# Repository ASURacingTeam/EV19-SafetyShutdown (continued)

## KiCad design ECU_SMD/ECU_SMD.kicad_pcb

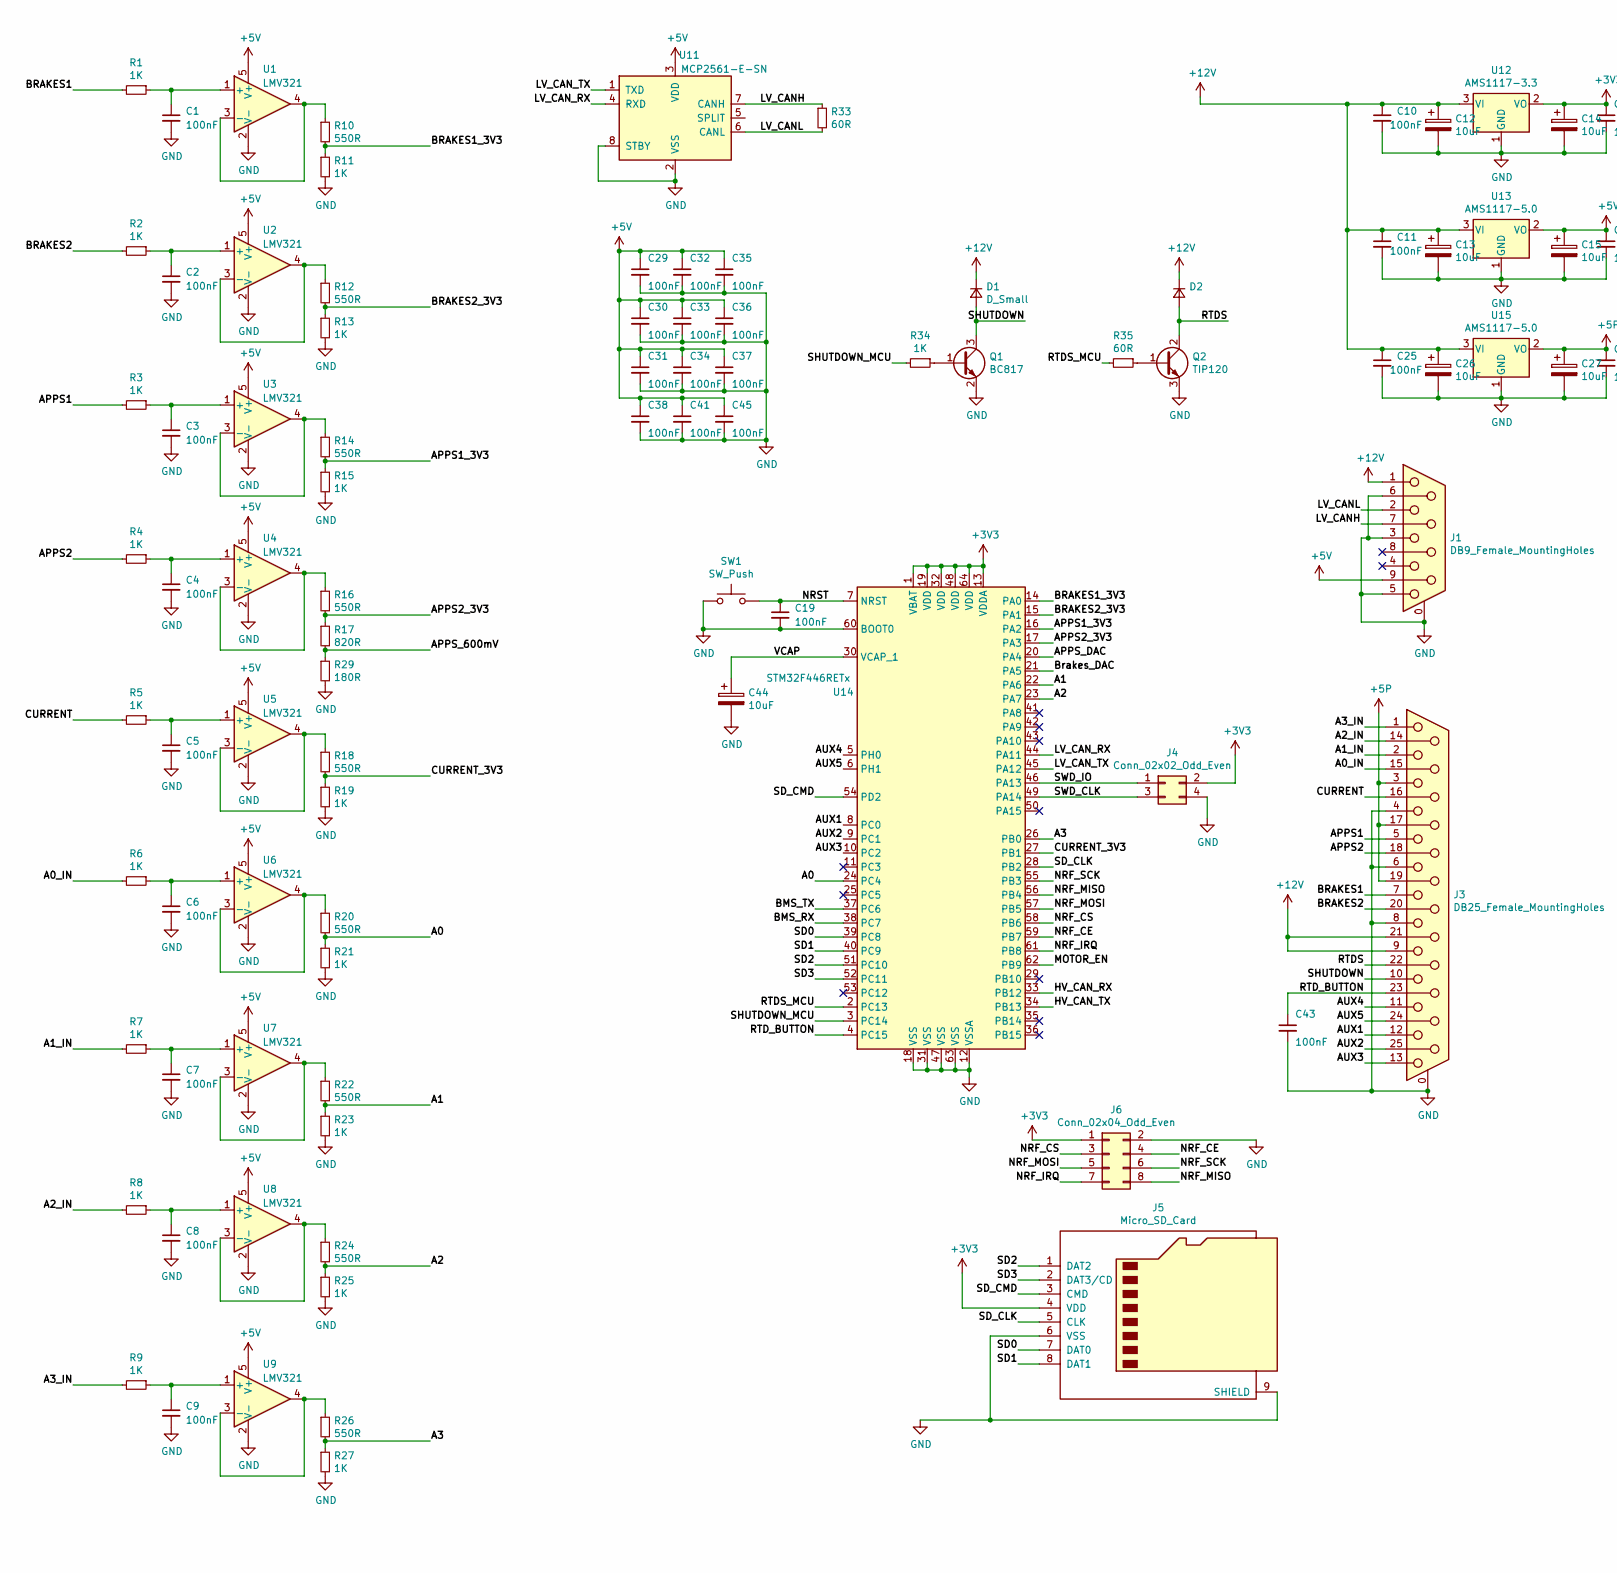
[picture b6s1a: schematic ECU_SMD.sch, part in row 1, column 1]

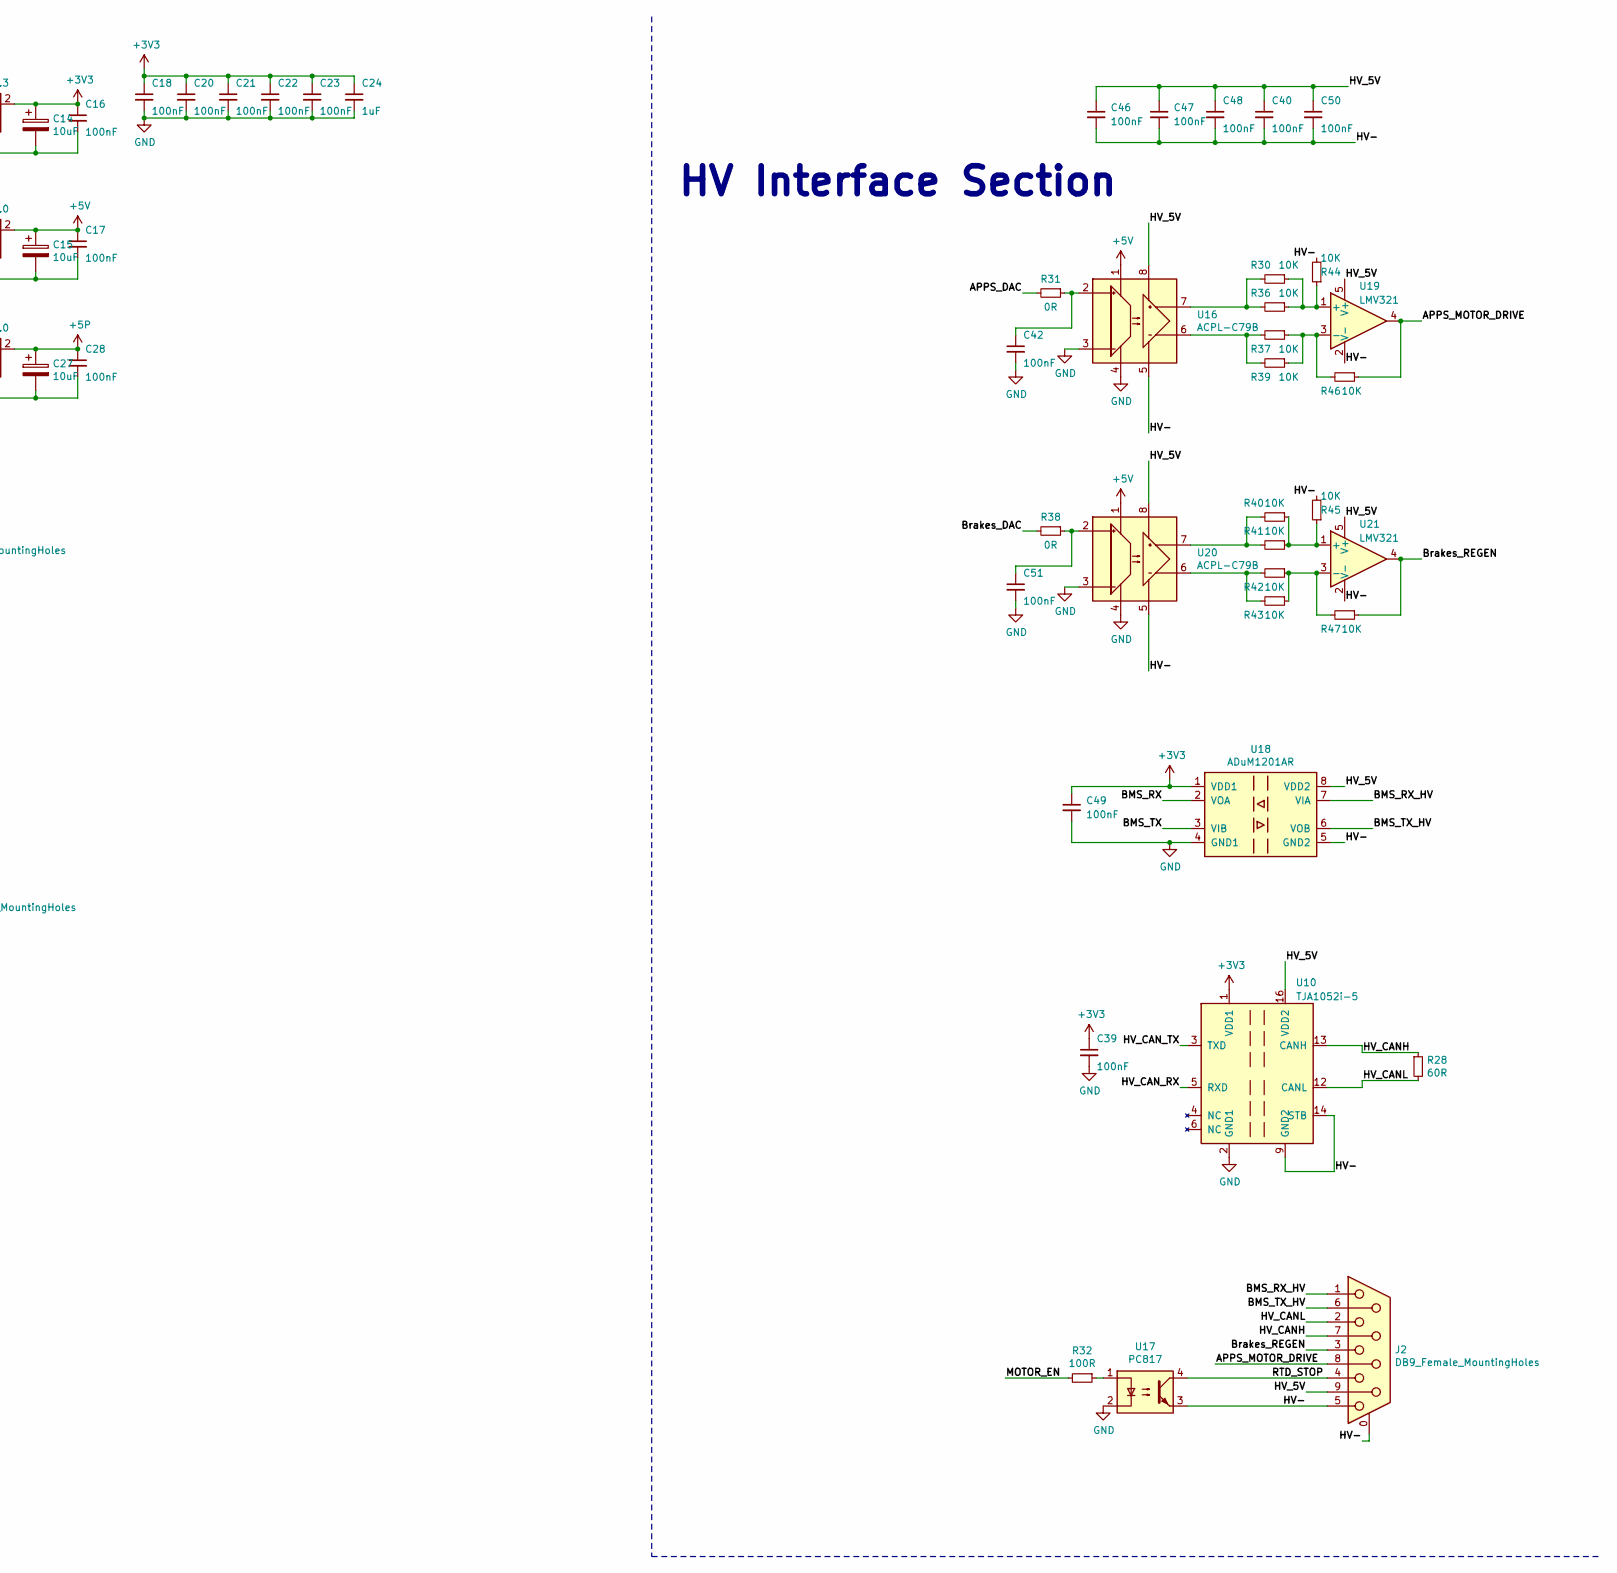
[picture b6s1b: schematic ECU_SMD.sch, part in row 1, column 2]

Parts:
C1, C2, C3, C4, C5, C6, C7, C8, C9, C10, C11, C16, C17, C18, C19, C20, C21, C22, C23, C25, C28, C29, C30, C31, C32, C33, C34, C35, C36, C37, C38, C39, C40, C41, C42, C43, C45, C46, C47, C48, C49, C50, C51: 100nF; C_0805_2012Metric_Pad1.15x1.40mm_HandSolder
C12, C13, C14, C15, C26, C27, C44: 10uF; C_1206_3216Metric_Pad1.42x1.75mm_HandSolder
C24: 1uF; C_0805_2012Metric_Pad1.15x1.40mm_HandSolder
D1: D_Small; D_A-405_P10.16mm_Horizontal
D2: a; D_A-405_P10.16mm_Horizontal
J1, J2: DB9_Female_MountingHoles; DSUB-9_Female_Horizontal_P2.77x2.84mm_EdgePinOffset4.94mm_H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
J3: DB25_Female_MountingHoles; DSUB-25_Female_Horizontal_P2.77x2.84mm_EdgePinOffset4.94mm_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
J4: Conn_02x02_Odd_Even; PinHeader_2x02_P2.54mm_Vertical
J5: Micro_SD_Card; microSD_HC_Hirose_DM3AT-SF-PEJM5
J6: Conn_02x04_Odd_Even; PinHeader_2x04_P2.54mm_Vertical
Q1: BC817; SOT-23
Q2: TIP120; TO-220-3_Horizontal_TabDown
R1, R2, R3, R4, R5, R6, R7, R8, R9, R11, R13, R15, R19, R21, R23, R25, R27, R34: 1K; R_0805_2012Metric_Pad1.15x1.40mm_HandSolder
R10, R12, R14, R16, R18, R20, R22, R24, R26: 550R; R_0805_2012Metric_Pad1.15x1.40mm_HandSolder
R17: 820R; R_0805_2012Metric_Pad1.15x1.40mm_HandSolder
R28, R33, R35: 60R; R_0805_2012Metric_Pad1.15x1.40mm_HandSolder
R29: 180R; R_0805_2012Metric_Pad1.15x1.40mm_HandSolder
R30, R36, R37, R39, R40, R41, R42, R43, R44, R45, R46, R47: 10K; R_0805_2012Metric_Pad1.15x1.40mm_HandSolder
R31, R38: 0R; R_0805_2012Metric_Pad1.15x1.40mm_HandSolder
R32: 100R; R_0805_2012Metric_Pad1.15x1.40mm_HandSolder
SW1: SW_Push; R_0805_2012Metric_Pad1.15x1.40mm_HandSolder
U1, U2, U3, U4, U5, U6, U7, U8, U9, U19, U21: LMV321; SOT-23-5_HandSoldering
U10: TJA1052i-5; SOIC-16W_7.5x10.3mm_P1.27mm
U11: MCP2561-E-SN; SOIC-8_3.9x4.9mm_P1.27mm
U12: AMS1117-3.3; SOT-223-3_TabPin2
U13, U15: AMS1117-5.0; SOT-223-3_TabPin2
U14: STM32F446RETx; LQFP-64_10x10mm_P0.5mm
U16, U20: ACPL-C79B; SSO-8_6.8x5.9mm_P1.27mm_Clearance8mm
U17: PC817; DIP-4_W7.62mm
U18: ADuM1201AR; SOIC-8_3.9x4.9mm_P1.27mm

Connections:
+3V3: C14.1, C16.1, C18.1, C20.1, C21.1, C22.1, C23.1, C24.1, C39.1, C49.1, J4.2, J5.4 (VDD), J6.1, U10.1 (VDD1), U12.2 (VO), U14.1 (VBAT), U14.13 (VDDA), U14.19 (VDD), U14.32 (VDD), U14.48 (VDD), U14.64 (VDD), U18.1 (VDD1)
+5P: C27.1, C28.1, J3.3, J3.17, J3.19, U15.2 (VO)
+5V: C15.1, C17.1, C29.1, C30.1, C31.1, C32.1, C33.1, C34.1, C35.1, C36.1, C37.1, C38.1, C41.1, C45.1, J1.9, U1.5 (V+), U2.5 (V+), U3.5 (V+), U4.5 (V+), U5.5 (V+), U6.5 (V+), U7.5 (V+), U8.5 (V+), U9.5 (V+), U11.3 (VDD), U13.2 (VO), U16.1 (VDD1), U20.1 (VDD1)
+12V: C10.1, C11.1, C12.1, C13.1, C25.1, C26.1, D1.1 (K), D2.1 (K), J1.1, J3.9, J3.21, U12.3 (VI), U13.3 (VI), U15.3 (VI)
/A0: R20.2, R21.1, U14.24 (PC4)
/A0_IN: J3.15, R6.2
/A1: R22.2, R23.1, U14.22 (PA6)
/A1_IN: J3.2, R7.2
/A2: R24.2, R25.1, U14.23 (PA7)
/A2_IN: J3.14, R8.2
/A3: R26.2, R27.1, U14.26 (PB0)
/A3_IN: J3.1, R9.2
/APPS1: J3.5, R3.2
/APPS1_3V3: R14.2, R15.1, U14.16 (PA2)
/APPS2: J3.18, R4.2
/APPS2_3V3: R16.2, R17.1, U14.17 (PA3)
/APPS_600mV: R17.2, R29.1
/APPS_DAC: R31.2, U14.20 (PA4)
/APPS_MOTOR_DRIVE: J2.8, R46.1, U19.4
/AUX1: J3.12, U14.8 (PC0)
/AUX2: J3.25, U14.9 (PC1)
/AUX3: J3.13, U14.10 (PC2)
/AUX4: J3.11, U14.5 (PH0)
/AUX5: J3.24, U14.6 (PH1)
/BMS_RX: U14.38 (PC7), U18.2 (VOA)
/BMS_RX_HV: J2.1, U18.7 (VIA)
/BMS_TX: U14.37 (PC6), U18.3 (VIB)
/BMS_TX_HV: J2.6, U18.6 (VOB)
/BRAKES1: J3.7, R1.2
/BRAKES1_3V3: R10.2, R11.1, U14.14 (PA0)
/BRAKES2: J3.20, R2.2
/BRAKES2_3V3: R12.2, R13.1, U14.15 (PA1)
/Brakes_DAC: R38.2, U14.21 (PA5)
/Brakes_REGEN: J2.3, R47.1, U21.4
/CURRENT: J3.16, R5.2
/CURRENT_3V3: R18.2, R19.1, U14.27 (PB1)
/HV-: C40.2, C46.2, C47.2, C48.2, C50.2, J2.0 (PAD), J2.5, R44.2, R45.2, U10.9 (GND2), U10.10 (GND2), U10.14 (STB), U10.15 (GND2), U16.5 (GND2), U17.3, U18.5 (GND2), U19.2 (V-), U20.5 (GND2), U21.2 (V-)
/HV_5V: C40.1, C46.1, C47.1, C48.1, C50.1, J2.9, U10.11 (VDD2), U10.16 (VDD2), U16.8 (VDD2), U18.8 (VDD2), U19.5 (V+), U20.8 (VDD2), U21.5 (V+)
/HV_CANH: J2.7, R28.1, U10.13 (CANH)
/HV_CANL: J2.2, R28.2, U10.12 (CANL)
/HV_CAN_RX: U10.5 (RXD), U14.33 (PB12)
/HV_CAN_TX: U10.3 (TXD), U14.34 (PB13)
/LV_CANH: J1.7, R33.1, U11.7 (CANH)
/LV_CANL: J1.2, R33.2, U11.6 (CANL)
/LV_CAN_RX: U11.4 (RXD), U14.44 (PA11)
/LV_CAN_TX: U11.1 (TXD), U14.45 (PA12)
/MOTOR_EN: R32.2, U14.62 (PB9)
/NRF_CE: J6.4, U14.59 (PB7)
/NRF_CS: J6.3, U14.58 (PB6)
/NRF_IRQ: J6.7, U14.61 (PB8)
/NRF_MISO: J6.8, U14.56 (PB4)
/NRF_MOSI: J6.5, U14.57 (PB5)
/NRF_SCK: J6.6, U14.55 (PB3)
/NRST: C19.1, SW1.2, U14.7 (NRST)
/RTDS: D2.2 (A), J3.22, Q2.2 (C)
/RTDS_MCU: R35.2, U14.2 (PC13)
/RTD_BUTTON: C43.1, J3.23, U14.4 (PC15)
/RTD_STOP: J2.4, U17.4
/SD0: J5.7 (DAT0), U14.39 (PC8)
/SD1: J5.8 (DAT1), U14.40 (PC9)
/SD2: J5.1 (DAT2), U14.51 (PC10)
/SD3: J5.2 (DAT3/CD), U14.52 (PC11)
/SD_CLK: J5.5 (CLK), U14.28 (PB2)
/SD_CMD: J5.3 (CMD), U14.54 (PD2)
/SHUTDOWN: D1.2 (A), J3.10, Q1.3 (C)
/SHUTDOWN_MCU: R34.2, U14.3 (PC14)
/SWD_CLK: J4.3, U14.49 (PA14)
/SWD_IO: J4.1, U14.46 (PA13)
/VCAP: C44.1, U14.30 (VCAP_1)
GND: C1.2, C2.2, C3.2, C4.2, C5.2, C6.2, C7.2, C8.2, C9.2, C10.2, C11.2, C12.2, C13.2, C14.2, C15.2, C16.2, C17.2, C18.2, C19.2, C20.2, C21.2, C22.2, C23.2, C24.2, C25.2, C26.2, C27.2, C28.2, C29.2, C30.2, C31.2, C32.2, C33.2, C34.2, C35.2, C36.2, C37.2, C38.2, C39.2, C41.2, C42.2, C43.2, C44.2, C45.2, C49.2, C51.2, J1.0 (PAD), J1.3, J1.5, J1.6, J3.0 (PAD), J3.4, J3.6, J3.8, J4.4, J5.6 (VSS), J5.9 (SHIELD), J6.2, Q1.2 (E), Q2.3 (E), R11.2, R13.2, R15.2, R19.2, R21.2, R23.2, R25.2, R27.2, R29.2, SW1.1, U1.2 (V-), U2.2 (V-), U3.2 (V-), U4.2 (V-), U5.2 (V-), U6.2 (V-), U7.2 (V-), U8.2 (V-), U9.2 (V-), U10.2 (GND1), U10.7 (GND1), U10.8 (GND1), U11.2 (VSS), U11.8 (STBY), U12.1 (GND), U13.1 (GND), U14.12 (VSSA), U14.18 (VSS), U14.31 (VSS), U14.47 (VSS), U14.60 (BOOT0), U14.63 (VSS), U15.1 (GND), U16.3 (IN-), U16.4 (GND1), U17.2, U18.4 (GND1), U20.3 (IN-), U20.4 (GND1)
unnamed: C1.1, R1.1, U1.1 (+)
unnamed: C2.1, R2.1, U2.1 (+)
unnamed: C3.1, R3.1, U3.1 (+)
unnamed: C4.1, R4.1, U4.1 (+)
unnamed: C5.1, R5.1, U5.1 (+)
unnamed: C6.1, R6.1, U6.1 (+)
unnamed: C7.1, R7.1, U7.1 (+)
unnamed: C8.1, R8.1, U8.1 (+)
unnamed: C9.1, R9.1, U9.1 (+)
unnamed: C42.1, R31.1, U16.2 (IN+)
unnamed: C51.1, R38.1, U20.2 (IN+)
unnamed: Q1.1 (B), R34.1
unnamed: Q2.1 (B), R35.1
unnamed: R10.1, U1.3 (-), U1.4
unnamed: R12.1, U2.3 (-), U2.4
unnamed: R14.1, U3.3 (-), U3.4
unnamed: R16.1, U4.3 (-), U4.4
unnamed: R18.1, U5.3 (-), U5.4
unnamed: R20.1, U6.3 (-), U6.4
unnamed: R22.1, U7.3 (-), U7.4
unnamed: R24.1, U8.3 (-), U8.4
unnamed: R26.1, U9.3 (-), U9.4
unnamed 92: R30.1, R36.1, R44.1, U19.1 (+); also elsewhere on the board
unnamed 93: R30.2, R36.2, U16.7 (OUT+); also elsewhere on the board
unnamed: R32.1, U17.1
unnamed: R37.1, R39.1, R46.2, U19.3 (-)
unnamed: R37.2, R39.2, U16.6 (OUT-)
unnamed: R40.1, R41.1, R45.1, U21.1 (+)
unnamed: R40.2, R41.2, U20.7 (OUT+)
unnamed: R42.1, R43.1, R47.2, U21.3 (-)
unnamed: R42.2, R43.2, U20.6 (OUT-)

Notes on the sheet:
HV Interface Section

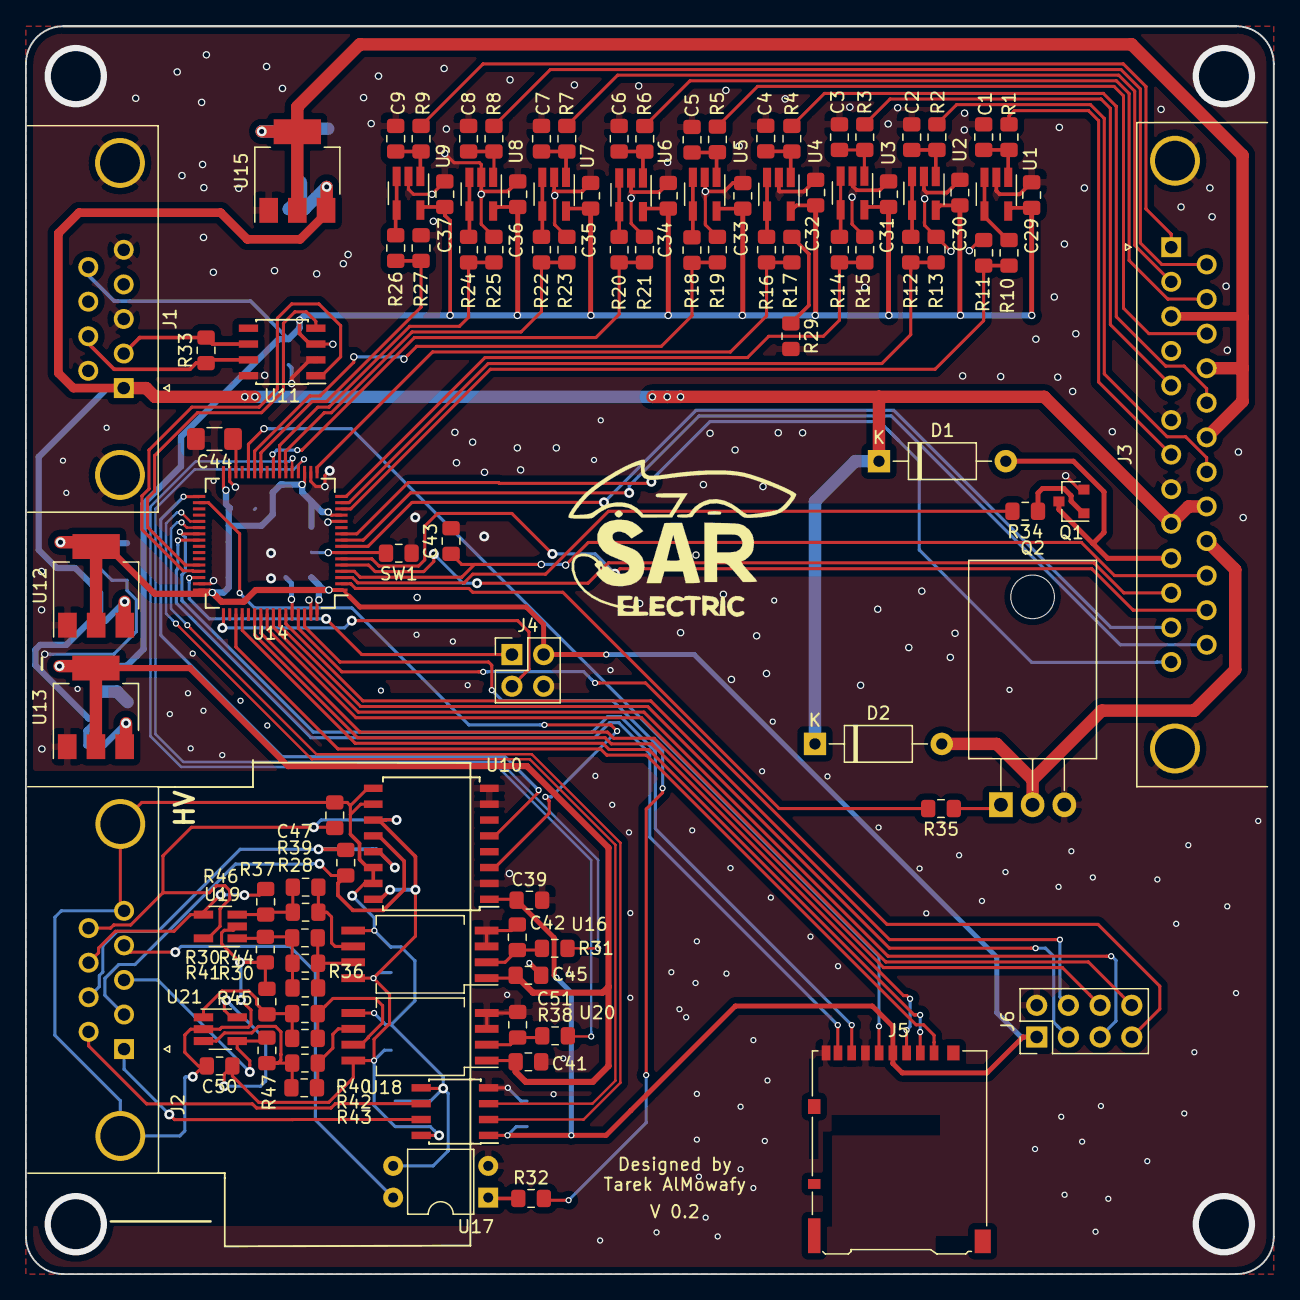
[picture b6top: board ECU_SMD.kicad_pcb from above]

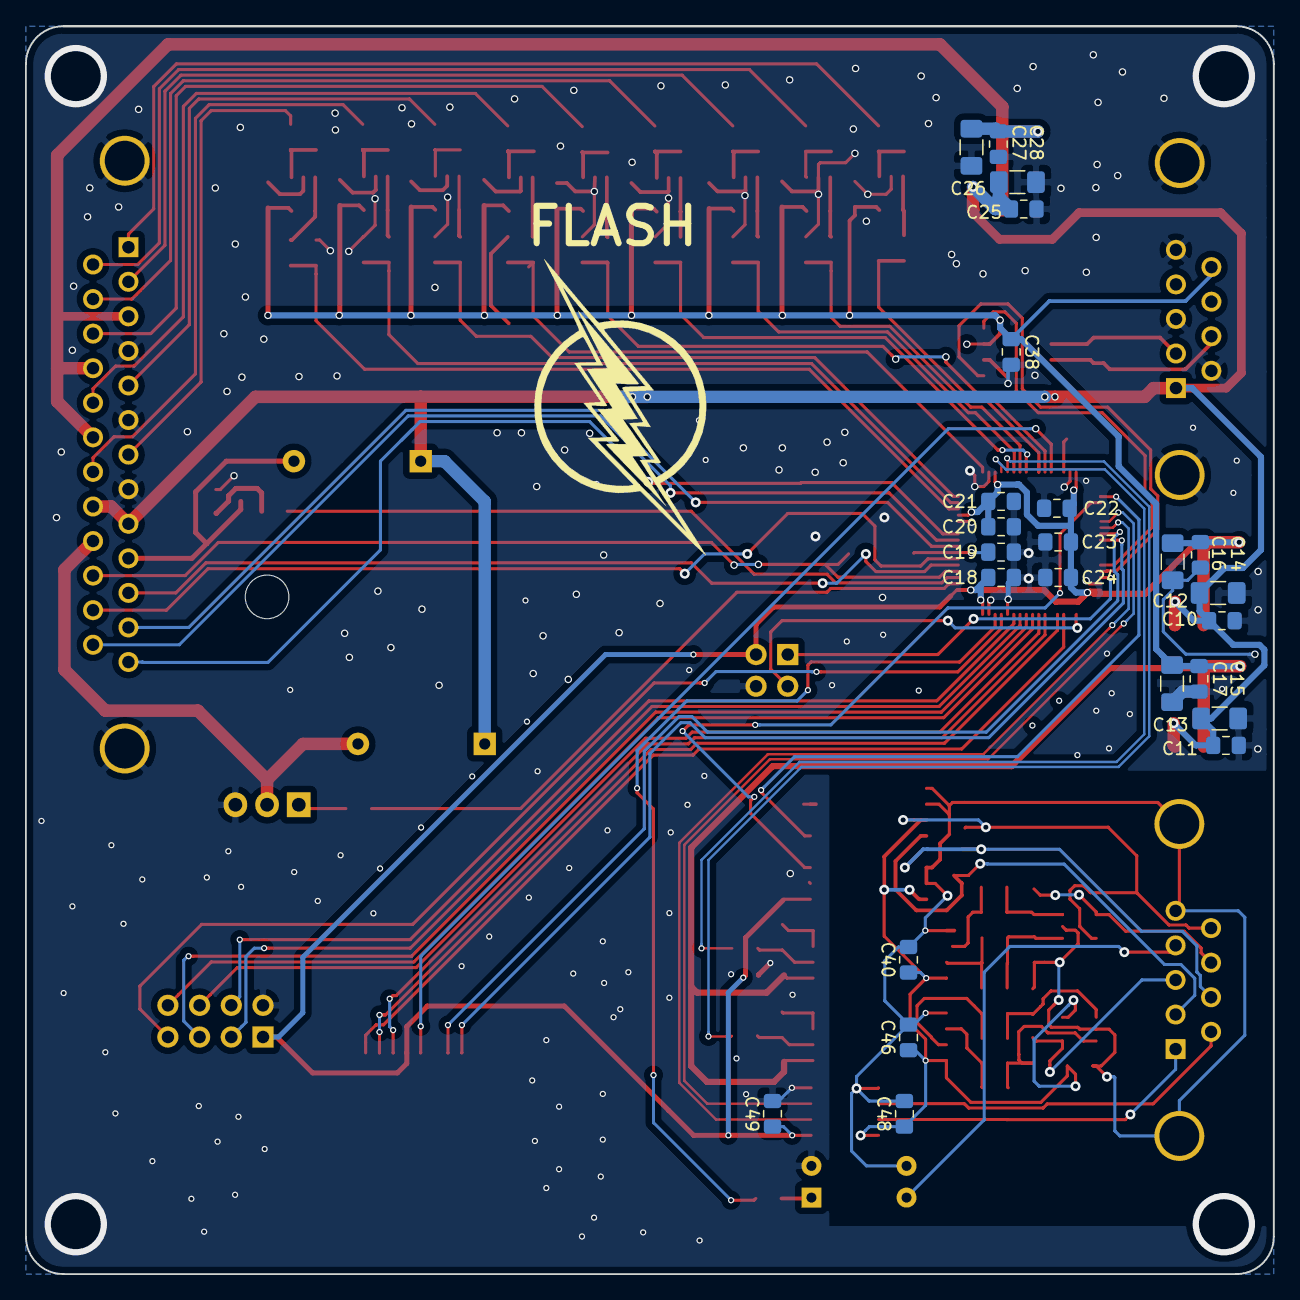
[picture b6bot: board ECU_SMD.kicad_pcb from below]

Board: 2 copper layers, 100.0 x 100.0 mm, 131 parts (24 on the bottom side), 101 nets.

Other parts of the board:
R30#2: 10K; R_0805_2012Metric_Pad1.15x1.40mm_HandSolder

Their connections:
unnamed 92: R30#2.1; also elsewhere on the board
unnamed 93: R30#2.2; also elsewhere on the board

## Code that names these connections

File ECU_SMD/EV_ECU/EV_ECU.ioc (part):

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Mcu.Name=STM32F446R(C-E)Tx
Mcu.Package=LQFP64
Mcu.UserName=STM32F446RETx
PA0-WKUP.GPIOParameters=GPIO_Label
PA0-WKUP.GPIO_Label=BRAKES1
PA0-WKUP.Signal=ADCx_IN0
PA1.GPIOParameters=GPIO_Label
PA1.GPIO_Label=BRAKES2
PA1.Signal=ADCx_IN1
PA11.Mode=Master
PA11.Signal=CAN1_RX
PA12.Mode=Master
PA12.Signal=CAN1_TX
PA13.Mode=Serial_Wire
PA13.Signal=SYS_JTMS-SWDIO
PA14.Mode=Serial_Wire
PA14.Signal=SYS_JTCK-SWCLK
PA2.GPIOParameters=GPIO_Label
PA2.GPIO_Label=APPS1
PA2.Signal=ADCx_IN2
PA3.GPIOParameters=GPIO_Label
PA3.GPIO_Label=APPS2
PA3.Signal=ADCx_IN3
PA4.GPIOParameters=GPIO_Label
PA4.GPIO_Label=APPS_OUT
PA4.Signal=COMP_DAC1_group
PA5.GPIOParameters=GPIO_Label
PA5.GPIO_Label=Brakes_OUT
PA5.Signal=COMP_DAC2_group
PA6.GPIOParameters=GPIO_Label
PA6.GPIO_Label=A1
PA6.Signal=ADCx_IN6
PA7.GPIOParameters=GPIO_Label
PA7.GPIO_Label=A2
PA7.Signal=ADCx_IN7
PB0.GPIOParameters=GPIO_Label
PB0.GPIO_Label=A3
PB0.Signal=ADCx_IN8
PB1.GPIOParameters=GPIO_Label
PB1.GPIO_Label=CURRENT
PB1.Signal=ADCx_IN9
PB12.Mode=Slave
PB12.Signal=CAN2_RX
PB13.Mode=Slave
PB13.Signal=CAN2_TX
PB2.GPIOParameters=GPIO_PuPd,GPIO_Label
PB2.GPIO_Label=SD_CLK
PB2.GPIO_PuPd=GPIO_PULLUP
PB2.Mode=SD_4_bits_Wide_bus
PB2.Signal=SDIO_CK
PB6.Mode=Asynchronous
PB6.Signal=USART1_TX
PB7.Mode=Asynchronous
PB7.Signal=USART1_RX
PB9.GPIOParameters=GPIO_Label
PB9.GPIO_Label=MOTOR_EN
PB9.Signal=GPIO_Output
PC0.GPIOParameters=GPIO_Label
PC0.GPIO_Label=AUX1
PC0.Signal=GPIO_Output
PC1.GPIOParameters=GPIO_Label
PC1.GPIO_Label=AUX2
PC1.Signal=GPIO_Output
PC10.GPIOParameters=GPIO_PuPd,GPIO_Label
PC10.GPIO_Label=SD2
PC10.GPIO_PuPd=GPIO_PULLUP
PC10.Mode=SD_4_bits_Wide_bus
PC10.Signal=SDIO_D2
PC11.GPIOParameters=GPIO_PuPd,GPIO_Label
PC11.GPIO_Label=SD3
PC11.GPIO_PuPd=GPIO_PULLUP
PC11.Mode=SD_4_bits_Wide_bus
PC11.Signal=SDIO_D3
PC13.GPIOParameters=GPIO_Label
PC13.GPIO_Label=RTDS
PC13.Signal=GPIO_Output
PC14-OSC32_IN.GPIOParameters=GPIO_Label
PC14-OSC32_IN.GPIO_Label=SHUTDOWN
PC14-OSC32_IN.Signal=GPIO_Output
PC15-OSC32_OUT.GPIOParameters=GPIO_PuPd,GPIO_Label
PC15-OSC32_OUT.GPIO_Label=RTD_BUTTON
PC15-OSC32_OUT.GPIO_PuPd=GPIO_PULLUP
PC15-OSC32_OUT.Signal=GPXTI15
PC2.GPIOParameters=GPIO_Label
PC2.GPIO_Label=AUX3
PC2.Signal=GPIO_Output
PC4.GPIOParameters=GPIO_Label
PC4.GPIO_Label=A0
PC4.Signal=ADCx_IN14
PC6.GPIOParameters=GPIO_Label
PC6.GPIO_Label=BMS_TX
PC6.Mode=Asynchronous
PC6.Signal=USART6_TX
PC7.GPIOParameters=GPIO_Label
PC7.GPIO_Label=BMS_RX
PC7.Mode=Asynchronous
PC7.Signal=USART6_RX
PC8.GPIOParameters=GPIO_PuPd,GPIO_Label
PC8.GPIO_Label=SD0
PC8.GPIO_PuPd=GPIO_PULLUP
PC8.Mode=SD_4_bits_Wide_bus
PC8.Signal=SDIO_D0
PC9.GPIOParameters=GPIO_PuPd,GPIO_Label
PC9.GPIO_Label=SD1
PC9.GPIO_PuPd=GPIO_PULLUP
PC9.Mode=SD_4_bits_Wide_bus
PC9.Signal=SDIO_D1
PD2.GPIOParameters=GPIO_PuPd,GPIO_Label
PD2.GPIO_Label=SD_CMD
PD2.GPIO_PuPd=GPIO_PULLUP
PD2.Mode=SD_4_bits_Wide_bus
PD2.Signal=SDIO_CMD
PH0-OSC_IN.GPIOParameters=GPIO_Label
PH0-OSC_IN.GPIO_Label=BMS_UART_TX_SOFT
PH0-OSC_IN.Signal=GPIO_Output
PH1-OSC_OUT.GPIOParameters=GPIO_Label
PH1-OSC_OUT.GPIO_Label=BMS_UART_RX_SOFT
PH1-OSC_OUT.Signal=GPIO_Input
RCC.SYSCLKFreq_VALUE=180000000
RCC.SYSCLKSource=RCC_SYSCLKSOURCE_PLLCLK
board=custom

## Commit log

2020-12-21 added the designs
